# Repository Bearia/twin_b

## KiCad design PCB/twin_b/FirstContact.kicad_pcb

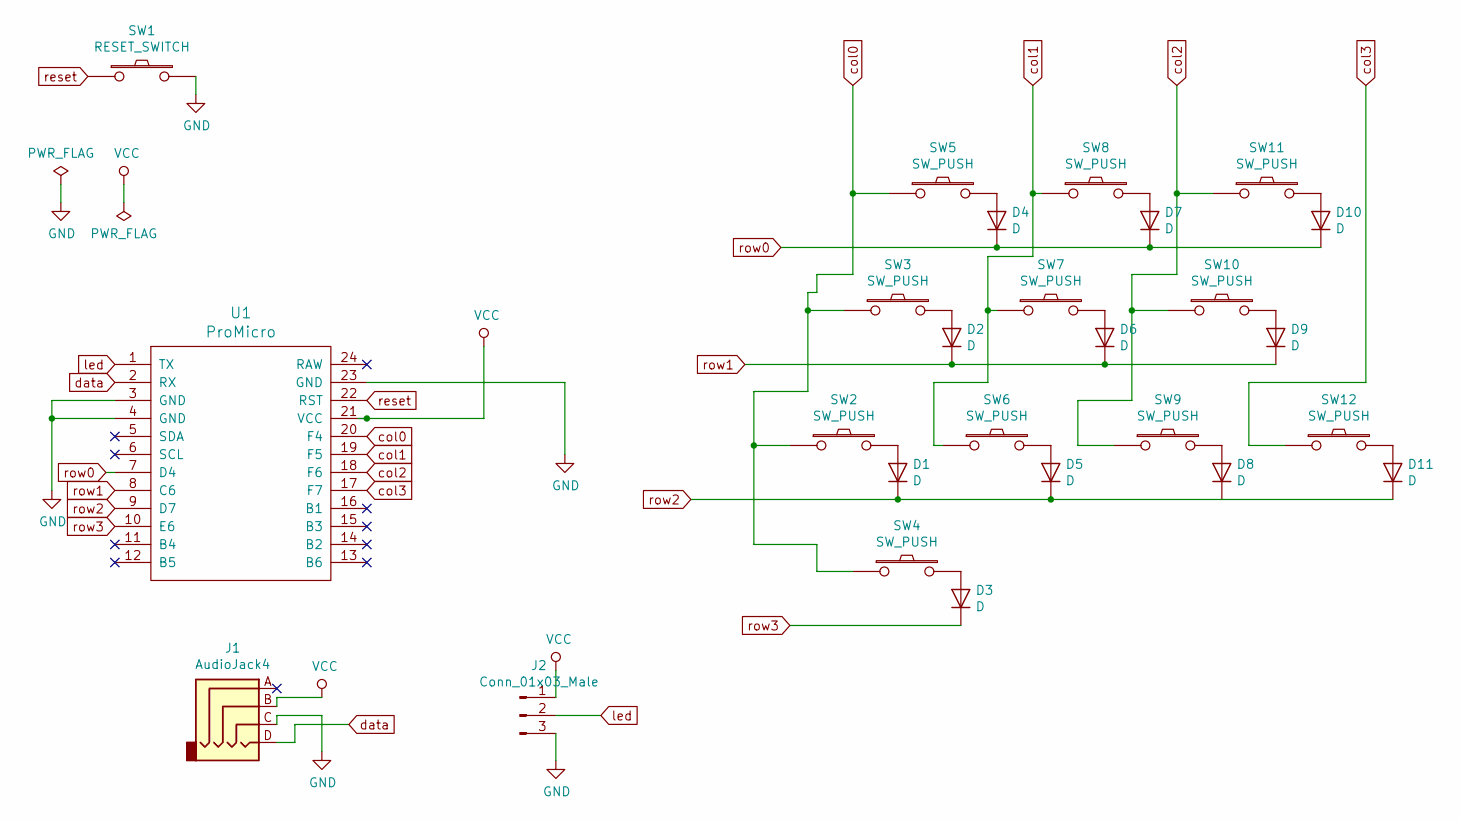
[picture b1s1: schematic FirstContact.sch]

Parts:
D1, D2, D3, D4, D5, D6, D7, D8, D9, D10, D11: D; D3_TH_SMD
J1: AudioJack4; MJ-4PP-9
J2: Conn_01x03_Male; StripLED_rev
SW1: RESET_SWITCH; ResetSW
SW2, SW3, SW4, SW5, SW6, SW7, SW8, SW9, SW10, SW11, SW12: SW_PUSH; CherryMX_MidHeight_Choc_Hotswap
U1: ProMicro; ProMicro_v2

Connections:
GND: J1.C, J2.3, SW1.2, U1.3 (GND), U1.4 (GND), U1.23 (GND)
unnamed: D1.2 (A), SW2.2
unnamed: D2.2 (A), SW3.2
unnamed: D3.2 (A), SW4.2
unnamed: D4.2 (A), SW5.2
unnamed: D5.2 (A), SW6.2
unnamed: D6.2 (A), SW7.2
unnamed: D7.2 (A), SW8.2
unnamed: D8.2 (A), SW9.2
unnamed: D9.2 (A), SW10.2
unnamed: D10.2 (A), SW11.2
unnamed: D11.2 (A), SW12.2
VCC: J1.B, J2.1, U1.21 (VCC)
col0: SW2.1, SW3.1, SW4.1, SW5.1, U1.20 (F4)
col1: SW6.1, SW7.1, SW8.1, U1.19 (F5)
col2: SW9.1, SW10.1, SW11.1, U1.18 (F6)
col3: SW12.1, U1.17 (F7)
data: J1.D, U1.2 (RX)
led: J2.2, U1.1 (TX)
reset: SW1.1, U1.22 (RST)
row0: D4.1 (K), D7.1 (K), D10.1 (K), U1.7 (D4)
row1: D2.1 (K), D6.1 (K), D9.1 (K), U1.8 (C6)
row2: D1.1 (K), D5.1 (K), D8.1 (K), D11.1 (K), U1.9 (D7)
row3: D3.1 (K), U1.10 (E6)

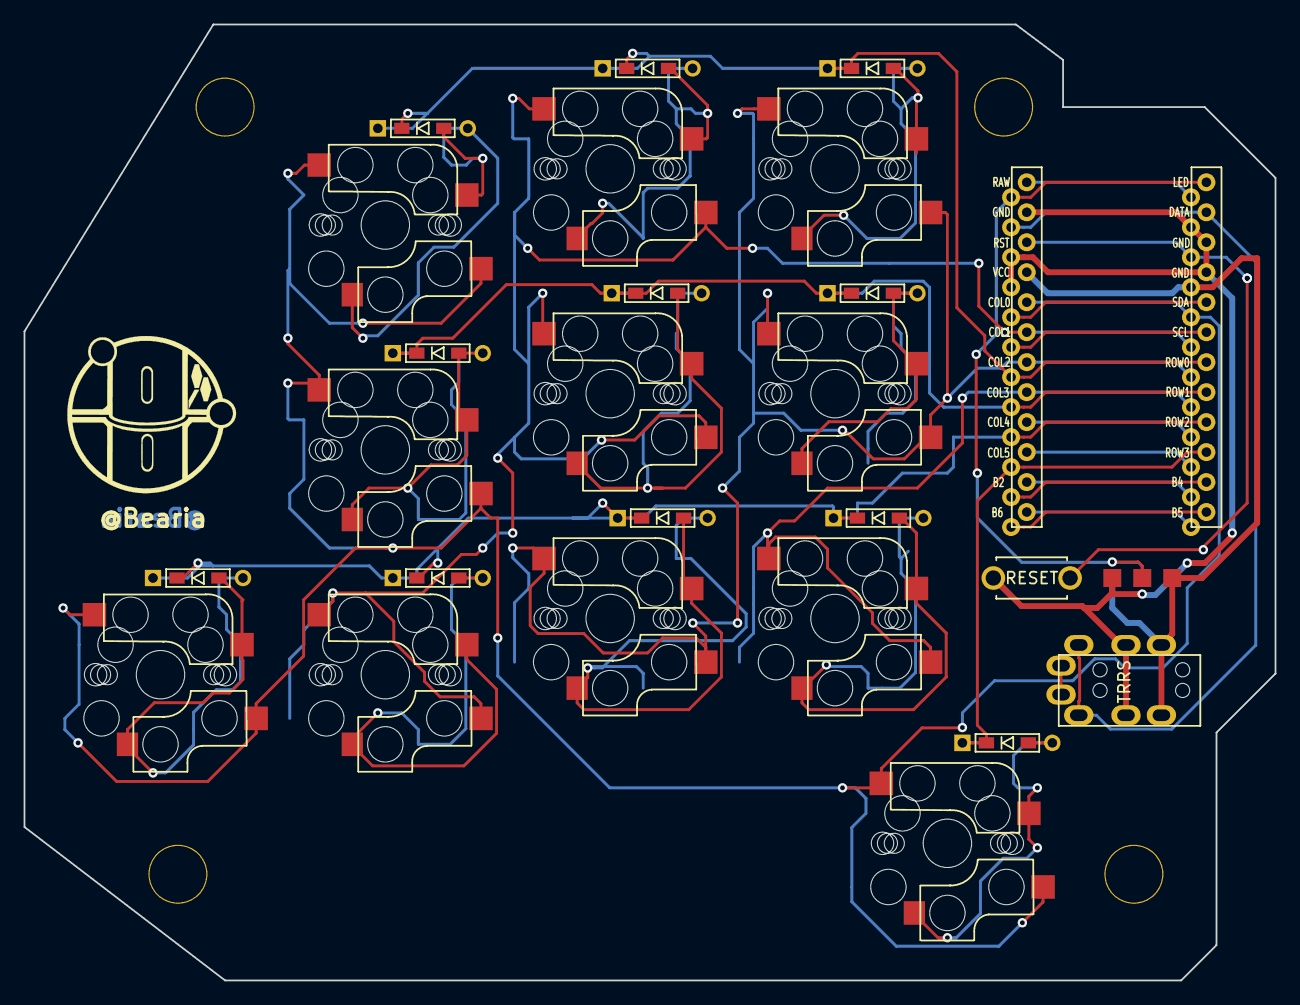
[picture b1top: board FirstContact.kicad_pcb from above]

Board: 2 copper layers, 106.0 x 81.0 mm, 30 parts (0 on the bottom side), 24 nets.

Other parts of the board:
Ref**: Val**; HOLE
Ref**#2, Ref**#3, Ref**#4: Val**; HOLE

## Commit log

2019-05-03 Update rules.mk
    Change "DEFAULT_FOLDER"
